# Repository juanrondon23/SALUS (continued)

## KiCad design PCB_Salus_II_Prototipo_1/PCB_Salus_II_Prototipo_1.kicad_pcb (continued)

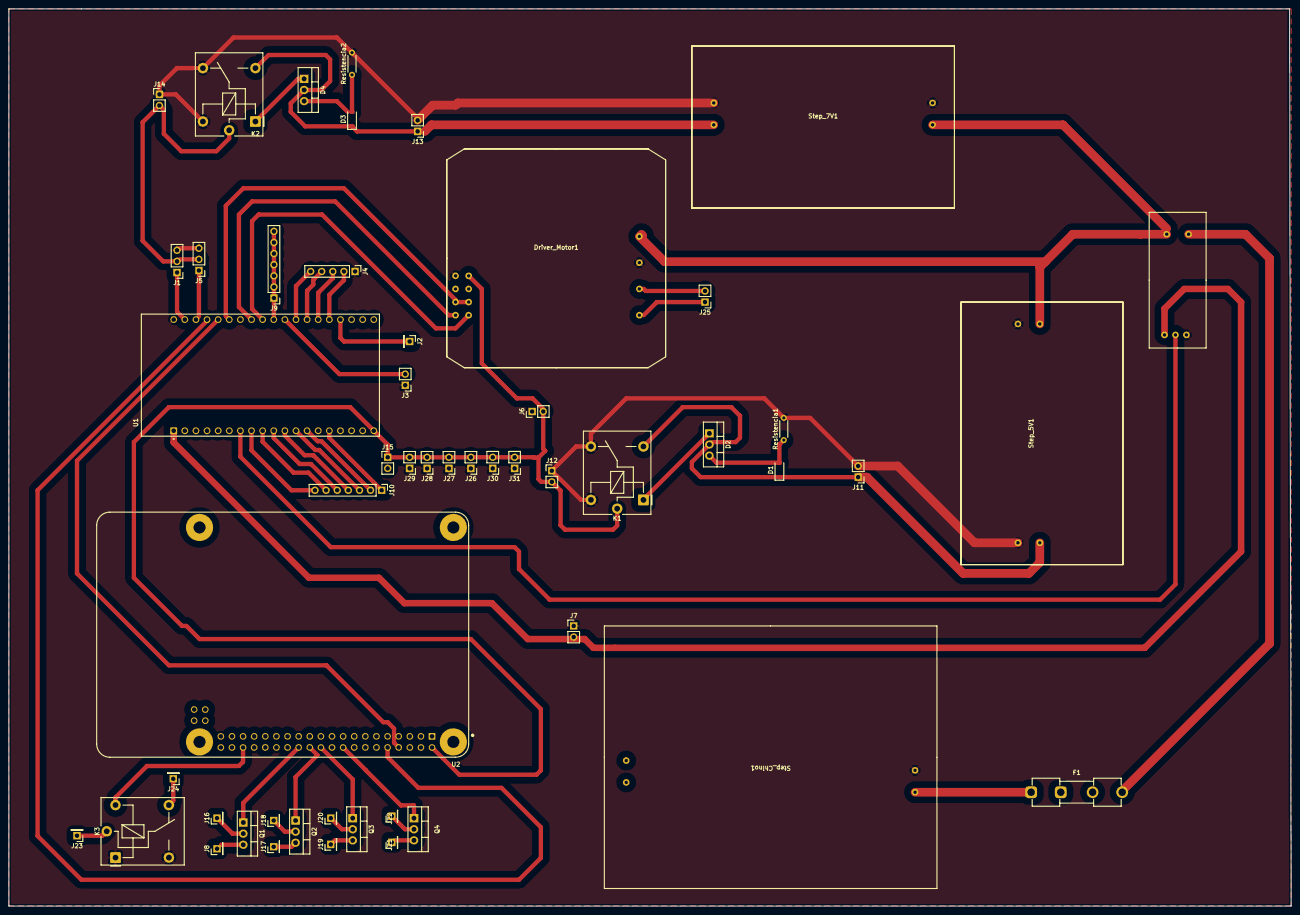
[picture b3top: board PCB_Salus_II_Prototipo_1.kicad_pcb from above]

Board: 2 copper layers, 293.0 x 205.0 mm, 52 parts (0 on the bottom side), 54 nets.

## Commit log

2025-06-18 Se agregan las primeras cosas de salus
2025-06-18 Queda por agregar los ultrasonidos
2025-06-18 Modifique la fuente de alimentacion de sensor de Corriente y de giro
2025-06-26 Se agrego sensores ultrasonidos
2025-06-27 Se agrego el codigo del cuatri y si empezo la programacion para la ESP32. Puntualmente se empezo con la comunicacion UART con RASP PI
2025-06-28 Se agrego OTA para la ESP32
2025-06-28 Pruebo github en visual
2025-06-30 Agregue la aceleracion del Cuatri con PixHawk, esto es con la funcion AnalogWrite
2025-06-30 Modifique las funciones que generan señales PWM en el ESP por recomendacion de COPILOT (Probar y si no funciona usar el anteriori)
2025-06-30 Se aplica logica del funcionamiento de Reversa
2025-08-26 Se prueba OTA y funciona, falta agregar SoftAP y STA
2025-09-04 Se prueba Branch
2025-09-04 Se agrega programacion via OTA con ESP como punto de acceso
2025-09-04 Se agrego Direccionn
2025-09-16 Se agrega modificacion de giro
2025-09-16 Probado la compilacion y arreglado los problemas
2025-09-16 se agrego la comunicacion serie por WiFi
2025-09-17 Se cambio la Ip para configurarlacon WiFi
2025-09-17 Se cambio contraseña del WiFi
2025-09-19 Se realizaron cambios de conexion de rele en Kicad
2025-09-19 Se mergeo Giro para solucionar errores y se modifico conexion de Rele
2025-09-19 Revert "Se mergeo Giro para solucionar errores y se modifico conexion de Rele"
    This reverts commit cd5eaa53754aee94d3ef285bc9ee5ec6b973b34c.
2025-09-19 se volvio al commit prueba para solucionar error
2025-09-19 se agrego mensaje para modificar conexion Rele
2025-09-19 cambie la contra del wifi
2025-10-24 Se comenzó con la PCB para SALUS III
2025-11-03 Se agrega Backups
2025-11-03 Se agregaron Modificaciones de PCB. Queda modificar raspy por tira de pines
2025-11-10 Parece ser la PCB definitiva de SALUS III por lo menos parte logica
2025-11-19 se agrego el diodo TVS a probar para proteger de cierres de Relé
2025-12-04 Cambios para realizarla en acido preparados
2025-12-04 pruebo primera vez esta branch
2025-12-04 PCB Hecha para ser enviada a China, falta revisar que esten todas las conexiones
2025-12-05 Mandar a China
2026-01-09 Se agrega Word con cosas necesarias para Salus IV
2026-01-12 Se agregan algunos cambios
2026-01-14 no se que cambio
2026-01-26 Documentacion de la investigacion para SALUS IV
2026-02-10 Se completo la investigacion y se agregaron simulaciones de Circuitos de proteccion
2026-02-11 Se comenzo con el diseño en Kicad y agregado de simbolos y huellas del proyecto
2026-02-13 se agrego logica de Rasp y algunos conectores
2026-02-19 pusheo por seguridad, avanzado Esquematico
2026-02-23 Agregamos Huellas y se dividio en hojas jerarquicas
2026-02-24 Se desarrollo el esquematico de la ESP32
2026-02-26 Se agregan cambios antes de agregar arrays
2026-03-04 Se agrega terminada antes de modificaciones de mejora
2026-03-05 Se guarda la PCB Salus IV ya terminada, queda revision final antes de envio
